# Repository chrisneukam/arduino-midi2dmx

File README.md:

# arduino-midi2dmx
MIDI to DMX protocol translator for lighting systems based on Arduino

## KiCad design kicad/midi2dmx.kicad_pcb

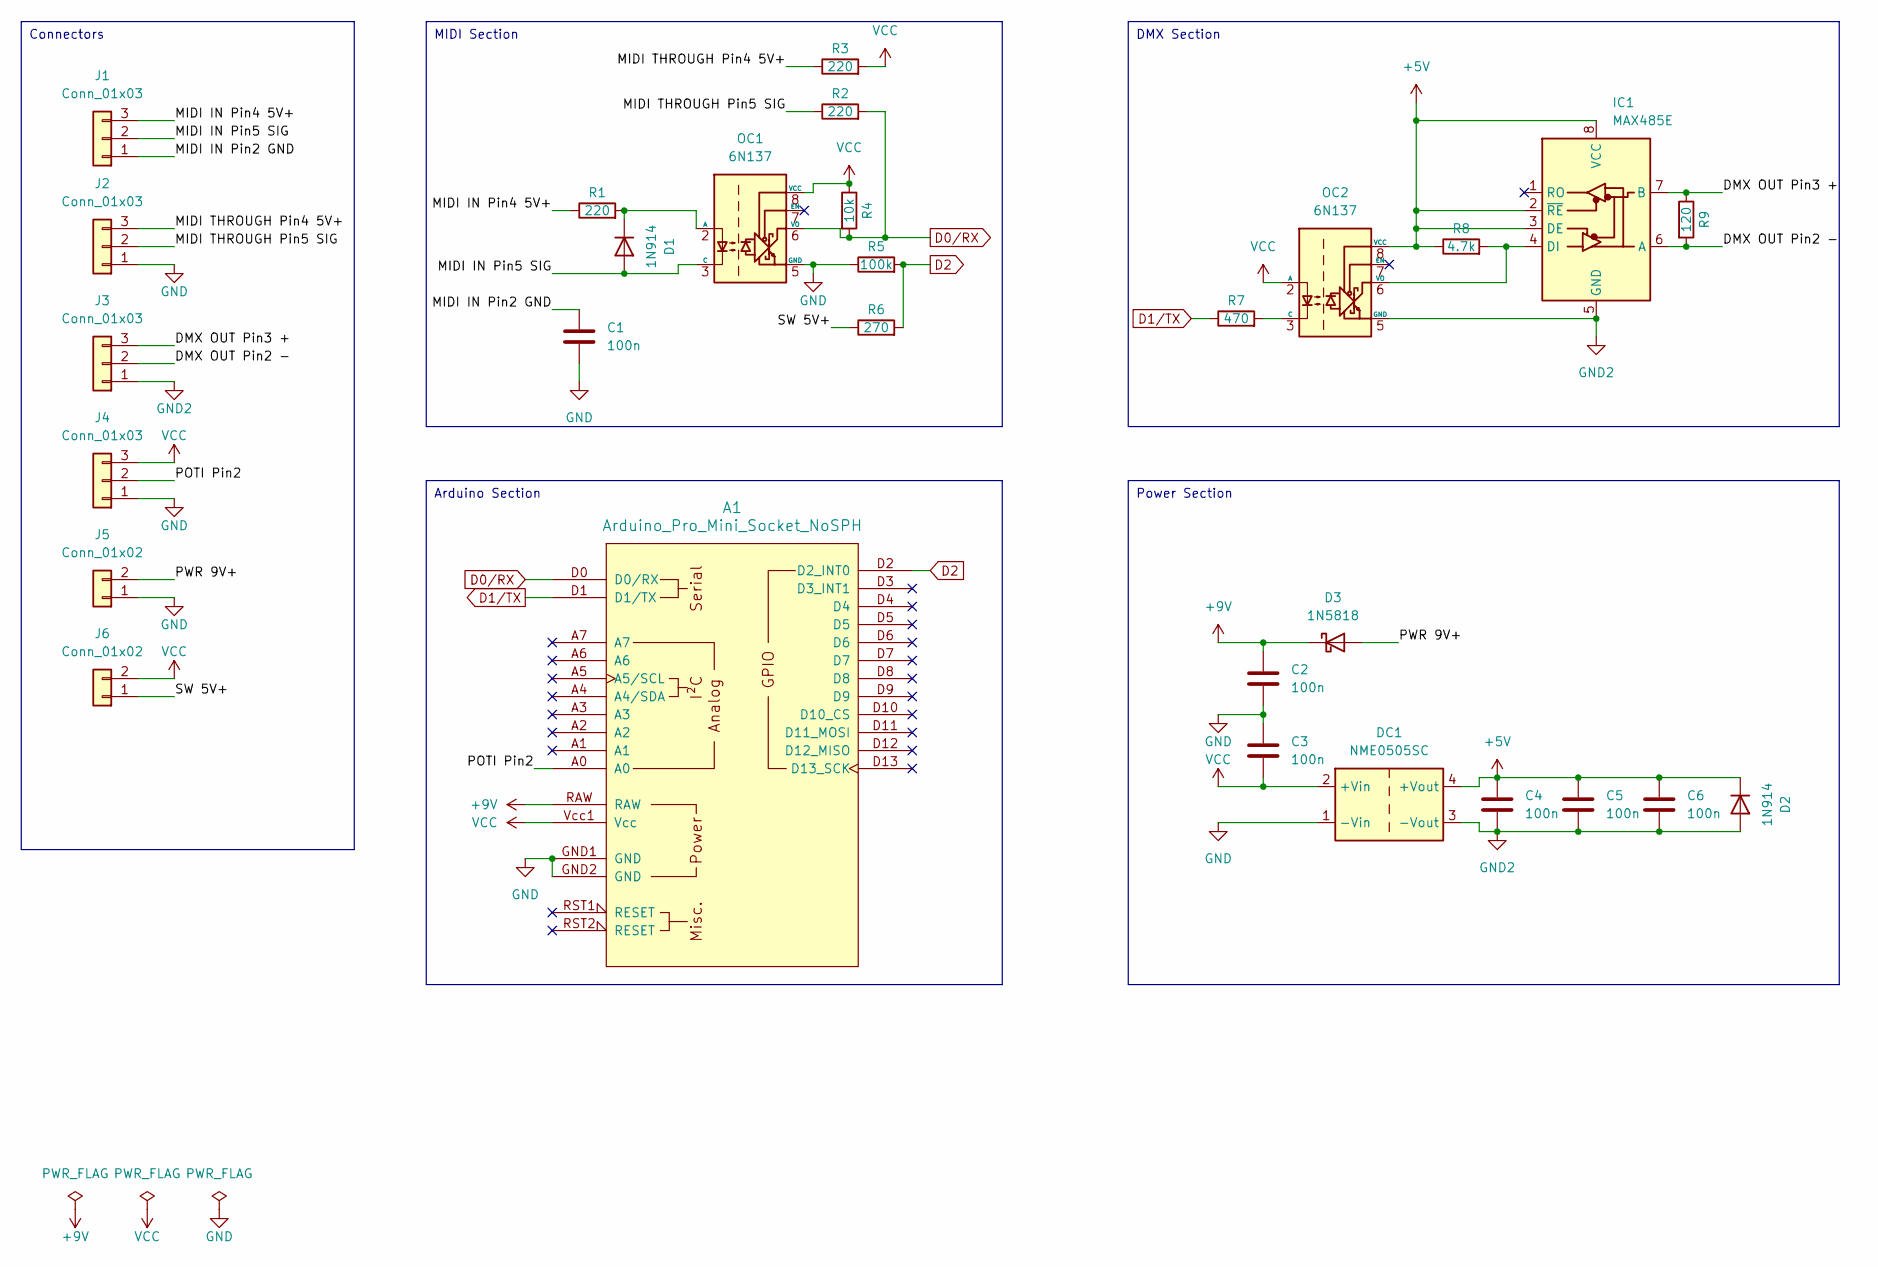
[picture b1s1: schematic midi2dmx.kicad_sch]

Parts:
A1: Arduino_Pro_Mini_Socket_NoSPH
C1, C2, C3, C4, C5, C6: 100n; C_1206_3216Metric
D1, D2: 1N914; D_1206_3216Metric
D3: 1N5818; D_1206_3216Metric
DC1: NME0505SC; Converter_DCDC_Murata_MEE1SxxxxSC_THT
IC1: MAX485E; SMDIP-8_W7.62mm
J1, J2, J3, J4: Conn_01x03; Molex_KK-254_AE-6410-03A_1x03_P2.54mm_Vertical
J5, J6: Conn_01x02; Molex_KK-254_AE-6410-02A_1x02_P2.54mm_Vertical
OC1, OC2: 6N137; SMDIP-8_W7.62mm
R1, R2, R3: 220; R_1206_3216Metric
R4: 10k; R_1206_3216Metric
R5: 100k; R_1206_3216Metric
R6: 270; R_1206_3216Metric
R7: 470; R_1206_3216Metric
R8: 4.7k; R_1206_3216Metric
R9: 120; R_1206_3216Metric

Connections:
+5V: C4.1, C5.1, C6.1, D2.1 (K), DC1.4 (+Vout), IC1.2 (~RE), IC1.3 (DE), IC1.8 (VCC), OC2.8 (VCC), R8.1
+9V: A1.RAW, C2.1, D3.1 (K)
/DMX OUT Pin2 -: IC1.6 (A), J3.2, R9.2
/DMX OUT Pin3 +: IC1.7 (B), J3.3, R9.1
/MIDI IN Pin2 GND: C1.1, J1.1
/MIDI IN Pin4 5V+: J1.3, R1.1
/MIDI IN Pin5 SIG: D1.2 (A), J1.2, OC1.3 (C)
/MIDI THROUGH Pin4 5V+: J2.3, R3.1
/MIDI THROUGH Pin5 SIG: J2.2, R2.1
/POTI Pin2: A1.A0, J4.2
/PWR 9V+: D3.2 (A), J5.2
/SW 5V+: J6.1, R6.1
D0/RX: A1.D0 (D0/RX), OC1.6 (VO), R2.2, R4.2
D1/TX: A1.D1 (D1/TX), R7.1
D2: A1.D2 (D2_INT0), R5.2, R6.2
GND: A1.GND1 (GND), A1.GND2 (GND), C1.2, C2.2, C3.1, DC1.1 (-Vin), J2.1, J4.1, J5.1, OC1.5 (GND), R5.1
GND2: C4.2, C5.2, C6.2, D2.2 (A), DC1.3 (-Vout), IC1.5 (GND), J3.1, OC2.5 (GND)
unnamed: D1.1 (K), OC1.2 (A), R1.2
unnamed: IC1.4 (DI), OC2.6 (VO), R8.2
unnamed: OC2.3 (C), R7.2
VCC: A1.Vcc1 (Vcc), C3.2, DC1.2 (+Vin), J4.3, J6.2, OC1.8 (VCC), OC2.2 (A), R3.2, R4.1

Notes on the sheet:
DMX Section
Arduino Section
MIDI Section
Power Section
Connectors

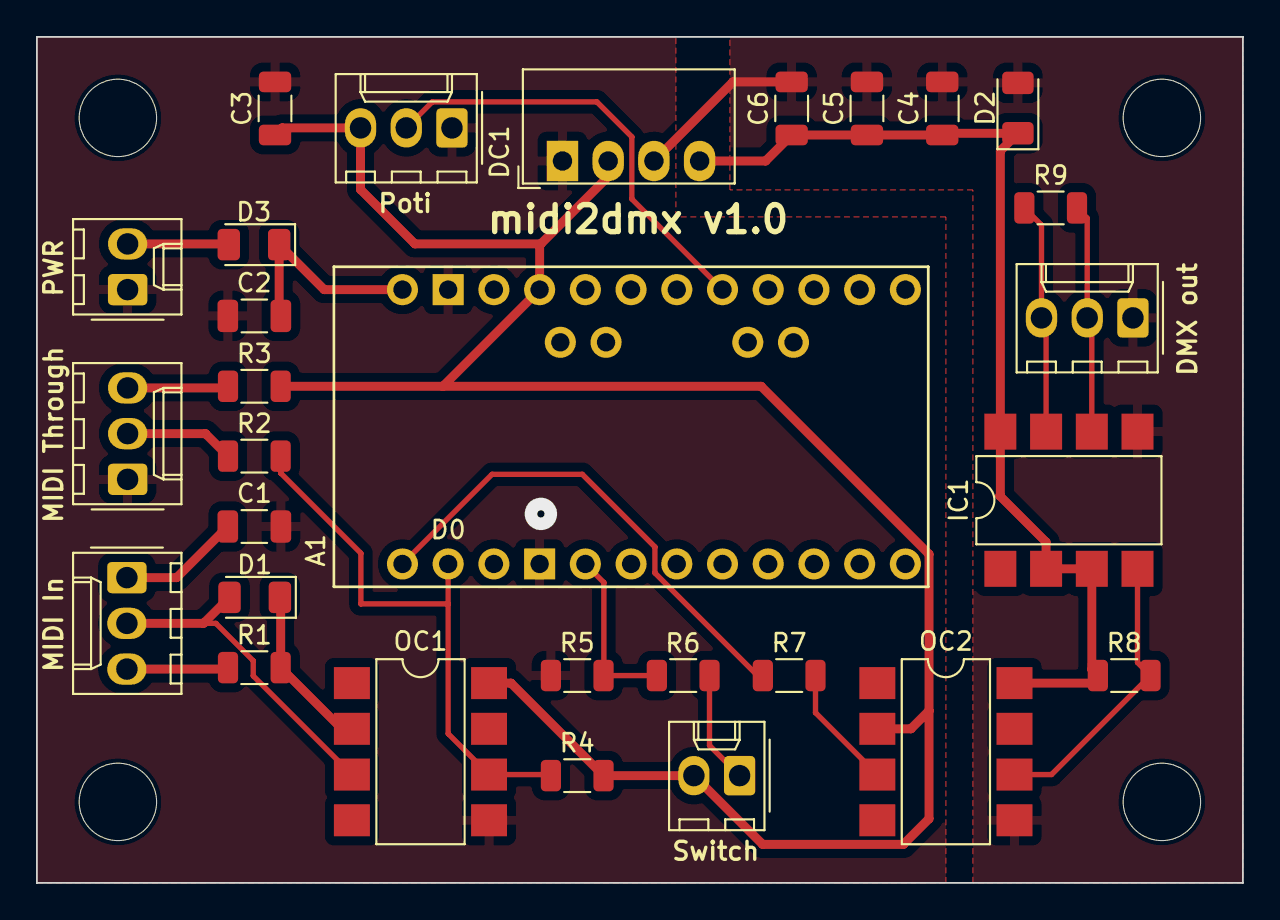
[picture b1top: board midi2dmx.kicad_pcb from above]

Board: 2 copper layers, 67.0 x 47.0 mm, 29 parts (0 on the bottom side), 21 nets.

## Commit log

2023-11-22 initial version of the schema
2023-11-22 update schematic
2023-12-13 add midi2dmx lib
2023-12-28 refactoring of DMX handling
2023-12-28 rework PCB to use SMD
2023-12-28 fix arduino build by removing C++ std header
2024-01-04 add midi reader
2024-01-08 add DMX override mode handling
2024-01-08 add Arduino examples
